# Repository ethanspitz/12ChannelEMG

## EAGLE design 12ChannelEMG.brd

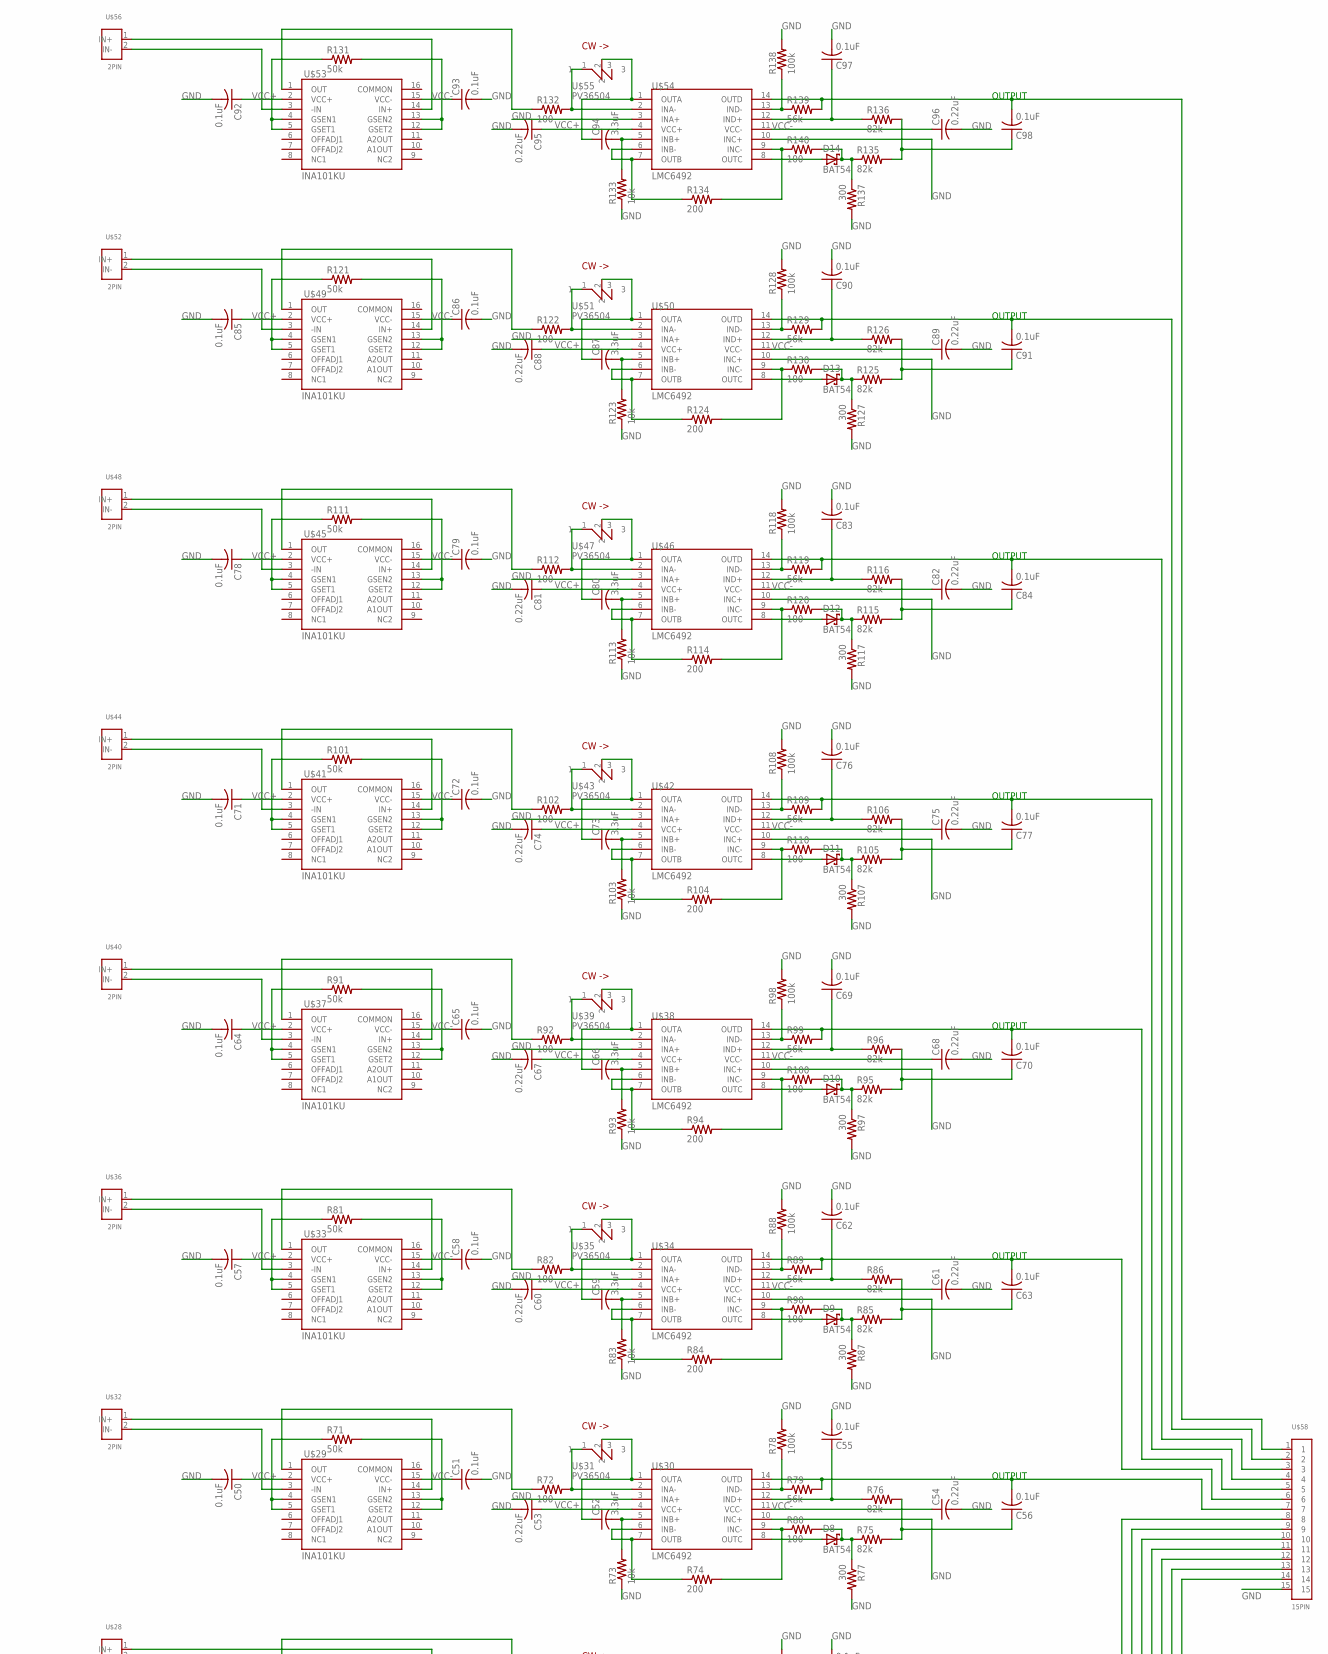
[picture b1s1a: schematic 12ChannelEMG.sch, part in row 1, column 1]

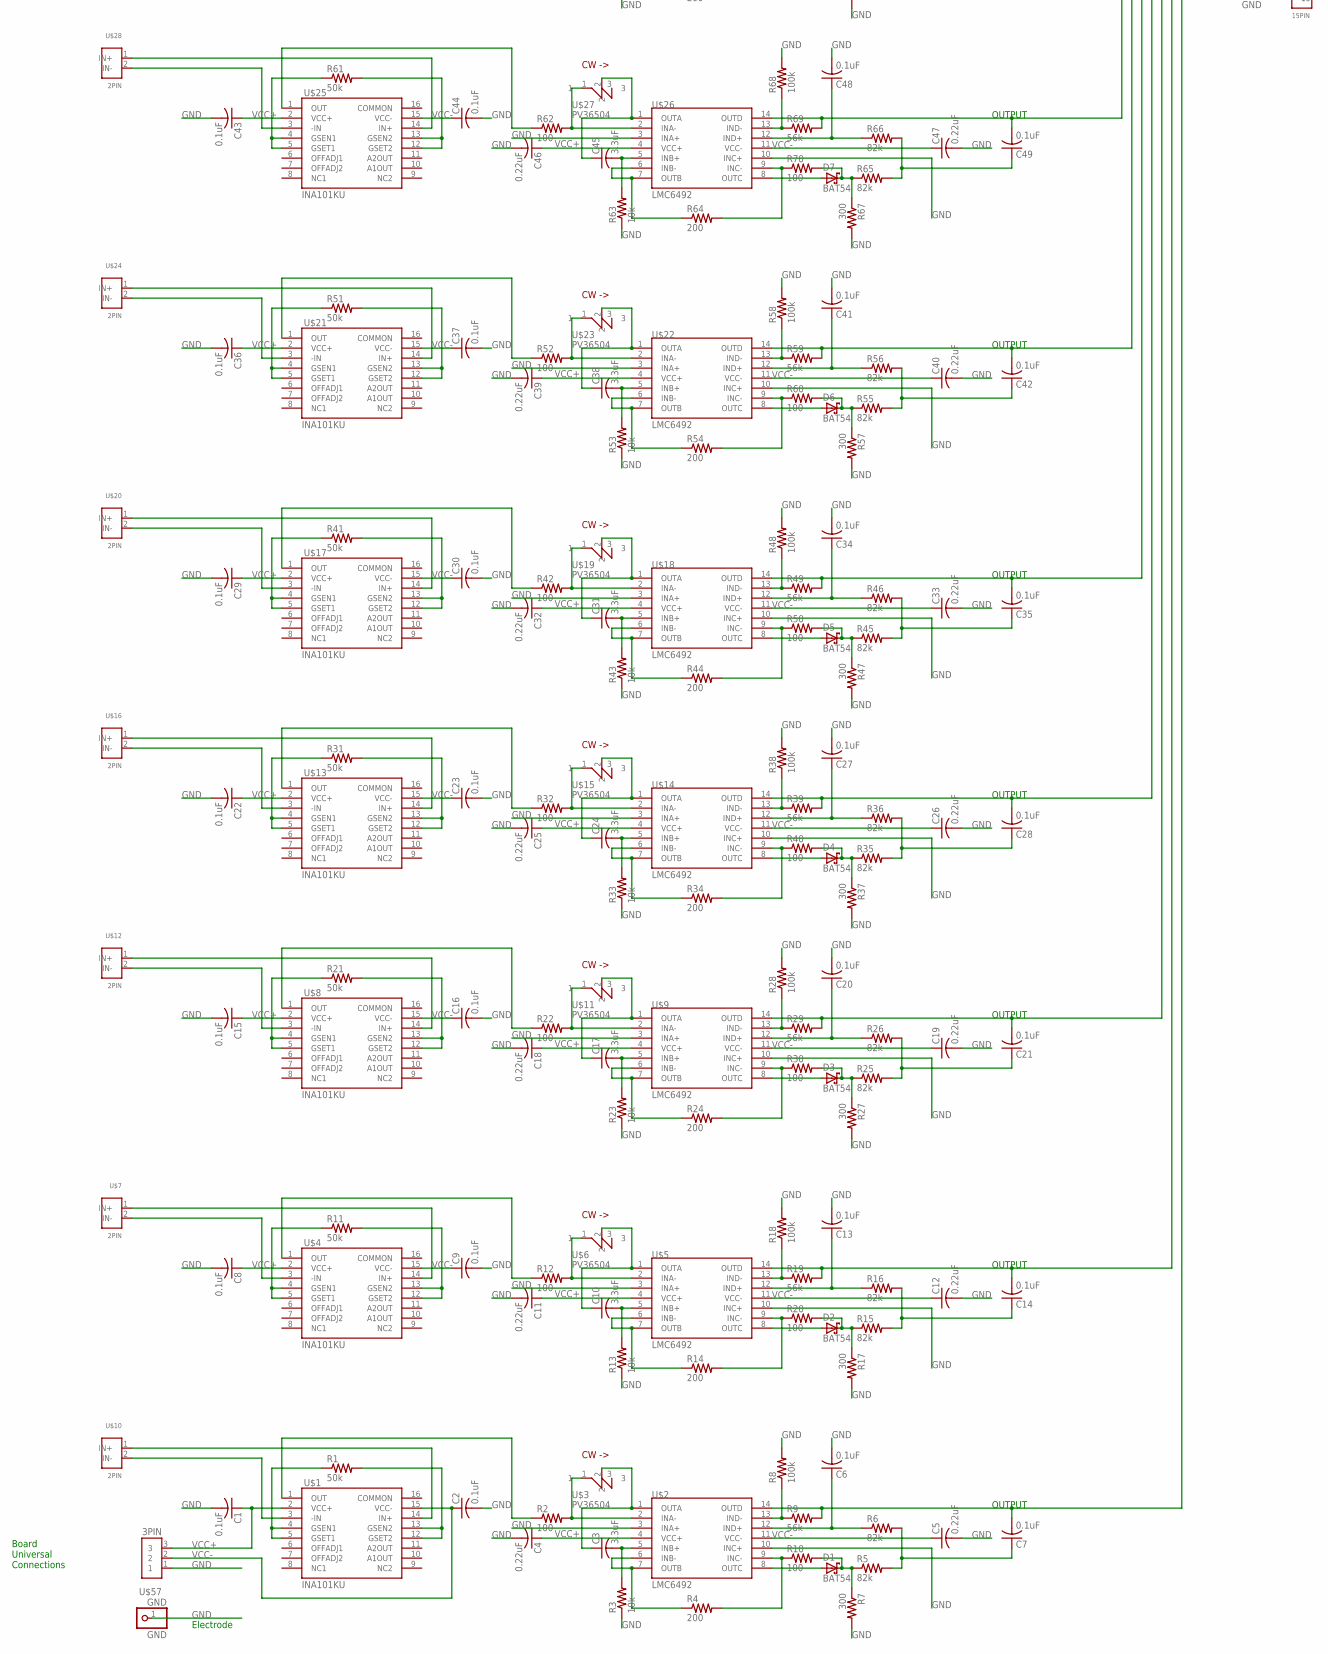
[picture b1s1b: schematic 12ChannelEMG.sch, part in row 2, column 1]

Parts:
C1, C2, C6, C7, C8, C9, C13, C14, C15, C16, C20, C21, C22, C23, C27, C28, C29, C30, C34, C35, C36, C37, C41, C42, C43, C44, C48, C49, C50, C51, C55, C56, C57, C58, C62, C63, C64, C65, C69, C70, C71, C72, C76, C77, C78, C79, C83, C84, C85, C86, C90, C91, C92, C93, C97, C98: 0.1uF; C1206K
C3, C10, C17, C24, C31, C38, C45, C52, C59, C66, C73, C80, C87, C94: 3.3uF; C1206K
C4, C5, C11, C12, C18, C19, C25, C26, C32, C33, C39, C40, C46, C47, C53, C54, C60, C61, C67, C68, C74, C75, C81, C82, C88, C89, C95, C96: 0.22uF; C0603K
D1, D2, D3, D4, D5, D6, D7, D8, D9, D10, D11, D12, D13, D14: BAT54; SOT23
GND: GND; 1X01
R1, R11, R21, R31, R41, R51, R61, R71, R81, R91, R101, R111, R121, R131: 50k; R0805
R2, R10, R12, R20, R22, R30, R32, R40, R42, R50, R52, R60, R62, R70, R72, R80, R82, R90, R92, R100, R102, R110, R112, R120, R122, R130, R132, R140: 100; R0603
R3, R13, R23, R33, R43, R53, R63, R73, R83, R93, R103, R113, R123, R133: 10k; R0603
R4, R14, R24, R34, R44, R54, R64, R74, R84, R94, R104, R114, R124, R134: 200; R0603
R5, R6, R15, R16, R25, R26, R35, R36, R45, R46, R55, R56, R65, R66, R75, R76, R85, R86, R95, R96, R105, R106, R115, R116, R125, R126, R135, R136: 82k; R0603
R7, R17, R27, R37, R47, R57, R67, R77, R87, R97, R107, R117, R127, R137: 300; R0603
R8, R18, R28, R38, R48, R58, R68, R78, R88, R98, R108, R118, R128, R138: 100k; R0603
R9, R19, R29, R39, R49, R59, R69, R79, R89, R99, R109, R119, R129, R139: 56k; R0603
U$1, U$4, U$8, U$13, U$17, U$21, U$25, U$29, U$33, U$37, U$41, U$45, U$49, U$53: INA101KU; SOIC167.5MM
U$2, U$5, U$9, U$14, U$18, U$22, U$26, U$30, U$34, U$38, U$42, U$46, U$50, U$54: LMC6492; SOIC14
U$3, U$6, U$11, U$15, U$19, U$23, U$27, U$31, U$35, U$39, U$43, U$47, U$51, U$55: PV36504; PV36W
U$7, U$10, U$12, U$16, U$20, U$24, U$28, U$32, U$36, U$40, U$44, U$48, U$52, U$56: 2PIN
U$57: 3PIN
U$58: 15PIN

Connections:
GND: C1.2, C2.2, C4.2, C5.2, C6.2, C8.2, C9.2, C11.2, C12.2, C13.2, C15.2, C16.2, C18.2, C19.2, C20.2, C22.2, C23.2, C25.2, C26.2, C27.2, C29.2, C30.2, C32.2, C33.2, C34.2, C36.2, C37.2, C39.2, C40.2, C41.2, C43.2, C44.2, C46.2, C47.2, C48.2, C50.2, C51.2, C53.2, C54.2, C55.2, C57.2, C58.2, C60.2, C61.2, C62.2, C64.2, C65.2, C67.2, C68.2, C69.2, C71.2, C72.2, C74.2, C75.2, C76.2, C78.2, C79.2, C81.2, C82.2, C83.2, C85.2, C86.2, C88.2, C89.2, C90.2, C92.2, C93.2, C95.2, C96.2, C97.2, GND.1, R3.1, R7.2, R8.2, R13.1, R17.2, R18.2, R23.1, R27.2, R28.2, R33.1, R37.2, R38.2, R43.1, R47.2, R48.2, R53.1, R57.2, R58.2, R63.1, R67.2, R68.2, R73.1, R77.2, R78.2, R83.1, R87.2, R88.2, R93.1, R97.2, R98.2, R103.1, R107.2, R108.2, R113.1, R117.2, R118.2, R123.1, R127.2, R128.2, R133.1, R137.2, R138.2, U$2.3 (INA+), U$2.10 (INC+), U$5.3 (INA+), U$5.10 (INC+), U$9.3 (INA+), U$9.10 (INC+), U$14.3 (INA+), U$14.10 (INC+), U$18.3 (INA+), U$18.10 (INC+), U$22.3 (INA+), U$22.10 (INC+), U$26.3 (INA+), U$26.10 (INC+), U$30.3 (INA+), U$30.10 (INC+), U$34.3 (INA+), U$34.10 (INC+), U$38.3 (INA+), U$38.10 (INC+), U$42.3 (INA+), U$42.10 (INC+), U$46.3 (INA+), U$46.10 (INC+), U$50.3 (INA+), U$50.10 (INC+), U$54.3 (INA+), U$54.10 (INC+), U$57.1, U$58.15
unnamed: C3.1, U$2.1 (OUTA), U$3.2
unnamed: R1.2, U$1.12 (GSET2), U$1.13 (GSEN2)
unnamed: C3.2, R3.2, U$2.5 (INB+)
unnamed: R4.1, U$2.6 (INB-), U$2.7 (OUTB)
unnamed: R2.2, U$2.2 (INA-), U$3.1
unnamed: U$1.3 (-IN), U$10.2 (IN-)
unnamed: U$1.14 (IN+), U$10.1 (IN+)
unnamed: R2.1, U$1.1 (OUT)
unnamed: R4.2, R10.1, U$2.9 (INC-)
unnamed: D1.1 (A), U$2.8 (OUTC)
unnamed: C6.1, R6.1, U$2.12 (IND+)
unnamed: D1.3 (C), R5.1, R7.1, R10.2
unnamed: R11.2, U$4.12 (GSET2), U$4.13 (GSEN2)
unnamed: C7.2, R9.2, U$2.14 (OUTD), U$58.14
unnamed: R8.1, R9.1, U$2.13 (IND-)
unnamed: C7.1, R5.2, R6.2
unnamed: R1.1, U$1.4 (GSEN1), U$1.5 (GSET1)
unnamed: U$4.3 (-IN), U$7.2 (IN-)
unnamed: R12.2, U$5.2 (INA-), U$6.1
unnamed: R12.1, U$4.1 (OUT)
unnamed: C10.1, U$5.1 (OUTA), U$6.2
unnamed: C10.2, R13.2, U$5.5 (INB+)
unnamed: R14.1, U$5.6 (INB-), U$5.7 (OUTB)
unnamed: R14.2, R20.1, U$5.9 (INC-)
unnamed: D2.1 (A), U$5.8 (OUTC)
unnamed: C13.1, R16.1, U$5.12 (IND+)
unnamed: D2.3 (C), R15.1, R17.1, R20.2
unnamed: C14.2, R19.2, U$5.14 (OUTD), U$58.13
unnamed: R18.1, R19.1, U$5.13 (IND-)
unnamed: C14.1, R15.2, R16.2
unnamed: R11.1, U$4.4 (GSEN1), U$4.5 (GSET1)
unnamed: U$4.14 (IN+), U$7.1 (IN+)
unnamed: R21.2, U$8.12 (GSET2), U$8.13 (GSEN2)
unnamed: U$8.3 (-IN), U$12.2 (IN-)
unnamed: R22.2, U$9.2 (INA-), U$11.1
unnamed: R22.1, U$8.1 (OUT)
unnamed: C17.1, U$9.1 (OUTA), U$11.2
unnamed: C17.2, R23.2, U$9.5 (INB+)
unnamed: R24.1, U$9.6 (INB-), U$9.7 (OUTB)
unnamed: R24.2, R30.1, U$9.9 (INC-)
unnamed: D3.1 (A), U$9.8 (OUTC)
unnamed: C20.1, R26.1, U$9.12 (IND+)
unnamed: D3.3 (C), R25.1, R27.1, R30.2
unnamed: C21.2, R29.2, U$9.14 (OUTD), U$58.12
unnamed: R28.1, R29.1, U$9.13 (IND-)
unnamed: C21.1, R25.2, R26.2
unnamed: R21.1, U$8.4 (GSEN1), U$8.5 (GSET1)
unnamed: U$8.14 (IN+), U$12.1 (IN+)
unnamed: R31.2, U$13.12 (GSET2), U$13.13 (GSEN2)
unnamed: U$13.3 (-IN), U$16.2 (IN-)
unnamed: R32.2, U$14.2 (INA-), U$15.1
unnamed: R32.1, U$13.1 (OUT)
unnamed: C24.1, U$14.1 (OUTA), U$15.2
unnamed: C24.2, R33.2, U$14.5 (INB+)
unnamed: R34.1, U$14.6 (INB-), U$14.7 (OUTB)
unnamed: R34.2, R40.1, U$14.9 (INC-)
unnamed: D4.1 (A), U$14.8 (OUTC)
unnamed: C27.1, R36.1, U$14.12 (IND+)
unnamed: D4.3 (C), R35.1, R37.1, R40.2
unnamed: C28.2, R39.2, U$14.14 (OUTD), U$58.11
unnamed: R38.1, R39.1, U$14.13 (IND-)
unnamed: C28.1, R35.2, R36.2
unnamed: R31.1, U$13.4 (GSEN1), U$13.5 (GSET1)
unnamed: U$13.14 (IN+), U$16.1 (IN+)
unnamed: R41.2, U$17.12 (GSET2), U$17.13 (GSEN2)
unnamed: U$17.3 (-IN), U$20.2 (IN-)
unnamed: R42.2, U$18.2 (INA-), U$19.1
unnamed: R42.1, U$17.1 (OUT)
unnamed: C31.1, U$18.1 (OUTA), U$19.2
unnamed: C31.2, R43.2, U$18.5 (INB+)
unnamed: R44.1, U$18.6 (INB-), U$18.7 (OUTB)
unnamed: R44.2, R50.1, U$18.9 (INC-)
unnamed: D5.1 (A), U$18.8 (OUTC)
unnamed: C34.1, R46.1, U$18.12 (IND+)
unnamed: D5.3 (C), R45.1, R47.1, R50.2
unnamed: C35.2, R49.2, U$18.14 (OUTD), U$58.10
unnamed: R48.1, R49.1, U$18.13 (IND-)
unnamed: C35.1, R45.2, R46.2
unnamed: R41.1, U$17.4 (GSEN1), U$17.5 (GSET1)
unnamed: U$17.14 (IN+), U$20.1 (IN+)
unnamed: R51.2, U$21.12 (GSET2), U$21.13 (GSEN2)
unnamed: U$21.3 (-IN), U$24.2 (IN-)
unnamed: R52.2, U$22.2 (INA-), U$23.1
unnamed: R52.1, U$21.1 (OUT)
unnamed: C38.1, U$22.1 (OUTA), U$23.2
unnamed: C38.2, R53.2, U$22.5 (INB+)
unnamed: R54.1, U$22.6 (INB-), U$22.7 (OUTB)
unnamed: R54.2, R60.1, U$22.9 (INC-)
unnamed: D6.1 (A), U$22.8 (OUTC)
unnamed: C41.1, R56.1, U$22.12 (IND+)
unnamed: D6.3 (C), R55.1, R57.1, R60.2
unnamed: C42.2, R59.2, U$22.14 (OUTD), U$58.9
unnamed: R58.1, R59.1, U$22.13 (IND-)
unnamed: C42.1, R55.2, R56.2
unnamed: R51.1, U$21.4 (GSEN1), U$21.5 (GSET1)
unnamed: U$21.14 (IN+), U$24.1 (IN+)
unnamed: R61.2, U$25.12 (GSET2), U$25.13 (GSEN2)
unnamed: U$25.3 (-IN), U$28.2 (IN-)
unnamed: R62.2, U$26.2 (INA-), U$27.1
unnamed: R62.1, U$25.1 (OUT)
unnamed: C45.1, U$26.1 (OUTA), U$27.2
unnamed: C45.2, R63.2, U$26.5 (INB+)
unnamed: R64.1, U$26.6 (INB-), U$26.7 (OUTB)
unnamed: R64.2, R70.1, U$26.9 (INC-)
unnamed: D7.1 (A), U$26.8 (OUTC)
unnamed: C48.1, R66.1, U$26.12 (IND+)
unnamed: D7.3 (C), R65.1, R67.1, R70.2
unnamed: C49.2, R69.2, U$26.14 (OUTD), U$58.8
unnamed: R68.1, R69.1, U$26.13 (IND-)
unnamed: C49.1, R65.2, R66.2
unnamed: R61.1, U$25.4 (GSEN1), U$25.5 (GSET1)
unnamed: U$25.14 (IN+), U$28.1 (IN+)
unnamed: R71.2, U$29.12 (GSET2), U$29.13 (GSEN2)
unnamed: U$29.3 (-IN), U$32.2 (IN-)
unnamed: R72.2, U$30.2 (INA-), U$31.1
unnamed: R72.1, U$29.1 (OUT)
unnamed: C52.1, U$30.1 (OUTA), U$31.2
unnamed: C52.2, R73.2, U$30.5 (INB+)
unnamed: R74.1, U$30.6 (INB-), U$30.7 (OUTB)
unnamed: R74.2, R80.1, U$30.9 (INC-)
unnamed: D8.1 (A), U$30.8 (OUTC)
unnamed: C55.1, R76.1, U$30.12 (IND+)
unnamed: D8.3 (C), R75.1, R77.1, R80.2
unnamed: C56.2, R79.2, U$30.14 (OUTD), U$58.7
unnamed: R78.1, R79.1, U$30.13 (IND-)
unnamed: C56.1, R75.2, R76.2
unnamed: R71.1, U$29.4 (GSEN1), U$29.5 (GSET1)
unnamed: U$29.14 (IN+), U$32.1 (IN+)
unnamed: R81.2, U$33.12 (GSET2), U$33.13 (GSEN2)
unnamed: U$33.3 (-IN), U$36.2 (IN-)
unnamed: R82.2, U$34.2 (INA-), U$35.1
unnamed: R82.1, U$33.1 (OUT)
unnamed: C59.1, U$34.1 (OUTA), U$35.2
unnamed: C59.2, R83.2, U$34.5 (INB+)
unnamed: R84.1, U$34.6 (INB-), U$34.7 (OUTB)
unnamed: R84.2, R90.1, U$34.9 (INC-)
unnamed: D9.1 (A), U$34.8 (OUTC)
unnamed: C62.1, R86.1, U$34.12 (IND+)
unnamed: D9.3 (C), R85.1, R87.1, R90.2
unnamed: C63.2, R89.2, U$34.14 (OUTD), U$58.6
unnamed: R88.1, R89.1, U$34.13 (IND-)
unnamed: C63.1, R85.2, R86.2
unnamed: R81.1, U$33.4 (GSEN1), U$33.5 (GSET1)
unnamed: U$33.14 (IN+), U$36.1 (IN+)
unnamed: R91.2, U$37.12 (GSET2), U$37.13 (GSEN2)
unnamed: U$37.3 (-IN), U$40.2 (IN-)
unnamed: R92.2, U$38.2 (INA-), U$39.1
unnamed: R92.1, U$37.1 (OUT)
unnamed: C66.1, U$38.1 (OUTA), U$39.2
unnamed: C66.2, R93.2, U$38.5 (INB+)
unnamed: R94.1, U$38.6 (INB-), U$38.7 (OUTB)
unnamed: R94.2, R100.1, U$38.9 (INC-)
unnamed: D10.1 (A), U$38.8 (OUTC)
unnamed: C69.1, R96.1, U$38.12 (IND+)
unnamed: D10.3 (C), R95.1, R97.1, R100.2
unnamed: C70.2, R99.2, U$38.14 (OUTD), U$58.5
unnamed: R98.1, R99.1, U$38.13 (IND-)
unnamed: C70.1, R95.2, R96.2
unnamed: R91.1, U$37.4 (GSEN1), U$37.5 (GSET1)
unnamed: U$37.14 (IN+), U$40.1 (IN+)
unnamed: R101.2, U$41.12 (GSET2), U$41.13 (GSEN2)
unnamed: U$41.3 (-IN), U$44.2 (IN-)
unnamed: R102.2, U$42.2 (INA-), U$43.1
unnamed: R102.1, U$41.1 (OUT)
unnamed: C73.1, U$42.1 (OUTA), U$43.2
unnamed: C73.2, R103.2, U$42.5 (INB+)
unnamed: R104.1, U$42.6 (INB-), U$42.7 (OUTB)
unnamed: R104.2, R110.1, U$42.9 (INC-)
unnamed: D11.1 (A), U$42.8 (OUTC)
unnamed: C76.1, R106.1, U$42.12 (IND+)
unnamed: D11.3 (C), R105.1, R107.1, R110.2
unnamed: C77.2, R109.2, U$42.14 (OUTD), U$58.4
unnamed: R108.1, R109.1, U$42.13 (IND-)
unnamed: C77.1, R105.2, R106.2
unnamed: R101.1, U$41.4 (GSEN1), U$41.5 (GSET1)
unnamed: U$41.14 (IN+), U$44.1 (IN+)
unnamed: R111.2, U$45.12 (GSET2), U$45.13 (GSEN2)
unnamed: U$45.3 (-IN), U$48.2 (IN-)
unnamed: R112.2, U$46.2 (INA-), U$47.1
unnamed: R112.1, U$45.1 (OUT)
unnamed: C80.1, U$46.1 (OUTA), U$47.2
unnamed: C80.2, R113.2, U$46.5 (INB+)
unnamed: R114.1, U$46.6 (INB-), U$46.7 (OUTB)
unnamed: R114.2, R120.1, U$46.9 (INC-)
unnamed: D12.1 (A), U$46.8 (OUTC)
unnamed: C83.1, R116.1, U$46.12 (IND+)
unnamed: D12.3 (C), R115.1, R117.1, R120.2
unnamed: C84.2, R119.2, U$46.14 (OUTD), U$58.3
unnamed: R118.1, R119.1, U$46.13 (IND-)
unnamed: C84.1, R115.2, R116.2
unnamed: R111.1, U$45.4 (GSEN1), U$45.5 (GSET1)
unnamed: U$45.14 (IN+), U$48.1 (IN+)
unnamed: R121.2, U$49.12 (GSET2), U$49.13 (GSEN2)
unnamed: U$49.3 (-IN), U$52.2 (IN-)
unnamed: R122.2, U$50.2 (INA-), U$51.1
unnamed: R122.1, U$49.1 (OUT)
unnamed: C87.1, U$50.1 (OUTA), U$51.2
unnamed: C87.2, R123.2, U$50.5 (INB+)
unnamed: R124.1, U$50.6 (INB-), U$50.7 (OUTB)
unnamed: R124.2, R130.1, U$50.9 (INC-)
unnamed: D13.1 (A), U$50.8 (OUTC)
unnamed: C90.1, R126.1, U$50.12 (IND+)
unnamed: D13.3 (C), R125.1, R127.1, R130.2
unnamed: C91.2, R129.2, U$50.14 (OUTD), U$58.2
unnamed: R128.1, R129.1, U$50.13 (IND-)
unnamed: C91.1, R125.2, R126.2
unnamed: R121.1, U$49.4 (GSEN1), U$49.5 (GSET1)
unnamed: U$49.14 (IN+), U$52.1 (IN+)
unnamed: R131.2, U$53.12 (GSET2), U$53.13 (GSEN2)
unnamed: U$53.3 (-IN), U$56.2 (IN-)
unnamed: R132.2, U$54.2 (INA-), U$55.1
unnamed: R132.1, U$53.1 (OUT)
unnamed: C94.1, U$54.1 (OUTA), U$55.2
unnamed: C94.2, R133.2, U$54.5 (INB+)
unnamed: R134.1, U$54.6 (INB-), U$54.7 (OUTB)
unnamed: R134.2, R140.1, U$54.9 (INC-)
unnamed: D14.1 (A), U$54.8 (OUTC)
unnamed: C97.1, R136.1, U$54.12 (IND+)
unnamed: D14.3 (C), R135.1, R137.1, R140.2
unnamed: C98.2, R139.2, U$54.14 (OUTD), U$58.1
unnamed: R138.1, R139.1, U$54.13 (IND-)
unnamed: C98.1, R135.2, R136.2
unnamed: R131.1, U$53.4 (GSEN1), U$53.5 (GSET1)
unnamed: U$53.14 (IN+), U$56.1 (IN+)
VCC+: C1.1, C4.1, C8.1, C11.1, C15.1, C18.1, C22.1, C25.1, C29.1, C32.1, C36.1, C39.1, C43.1, C46.1, C50.1, C53.1, C57.1, C60.1, C64.1, C67.1, C71.1, C74.1, C78.1, C81.1, C85.1, C88.1, C92.1, C95.1, U$1.2 (VCC+), U$2.4 (VCC+), U$4.2 (VCC+), U$5.4 (VCC+), U$8.2 (VCC+), U$9.4 (VCC+), U$13.2 (VCC+), U$14.4 (VCC+), U$17.2 (VCC+), U$18.4 (VCC+), U$21.2 (VCC+), U$22.4 (VCC+), U$25.2 (VCC+), U$26.4 (VCC+), U$29.2 (VCC+), U$30.4 (VCC+), U$33.2 (VCC+), U$34.4 (VCC+), U$37.2 (VCC+), U$38.4 (VCC+), U$41.2 (VCC+), U$42.4 (VCC+), U$45.2 (VCC+), U$46.4 (VCC+), U$49.2 (VCC+), U$50.4 (VCC+), U$53.2 (VCC+), U$54.4 (VCC+), U$57.3
VCC-: C2.1, C5.1, C9.1, C12.1, C16.1, C19.1, C23.1, C26.1, C30.1, C33.1, C37.1, C40.1, C44.1, C47.1, C51.1, C54.1, C58.1, C61.1, C65.1, C68.1, C72.1, C75.1, C79.1, C82.1, C86.1, C89.1, C93.1, C96.1, U$1.15 (VCC-), U$2.11 (VCC-), U$4.15 (VCC-), U$5.11 (VCC-), U$8.15 (VCC-), U$9.11 (VCC-), U$13.15 (VCC-), U$14.11 (VCC-), U$17.15 (VCC-), U$18.11 (VCC-), U$21.15 (VCC-), U$22.11 (VCC-), U$25.15 (VCC-), U$26.11 (VCC-), U$29.15 (VCC-), U$30.11 (VCC-), U$33.15 (VCC-), U$34.11 (VCC-), U$37.15 (VCC-), U$38.11 (VCC-), U$41.15 (VCC-), U$42.11 (VCC-), U$45.15 (VCC-), U$46.11 (VCC-), U$49.15 (VCC-), U$50.11 (VCC-), U$53.15 (VCC-), U$54.11 (VCC-), U$57.2

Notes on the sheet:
Electrode
Board Universal Connections
OUTPUT

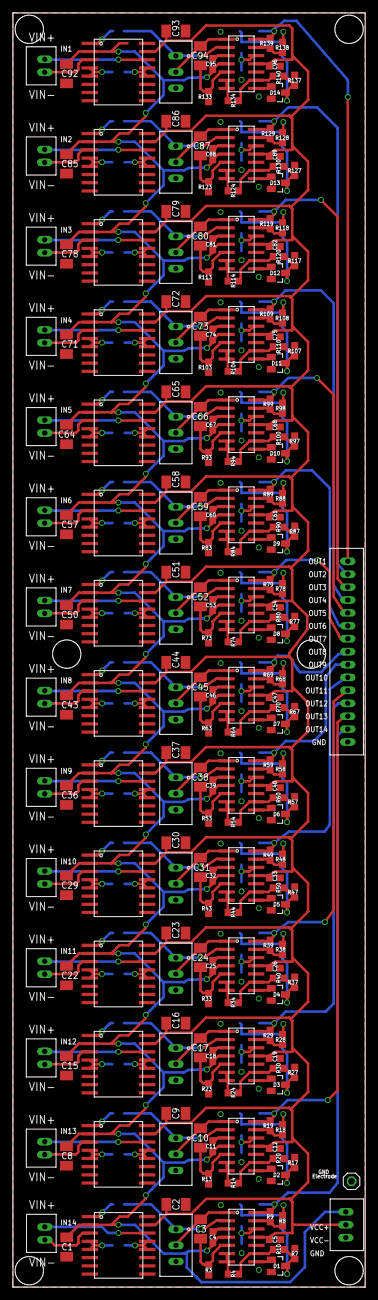
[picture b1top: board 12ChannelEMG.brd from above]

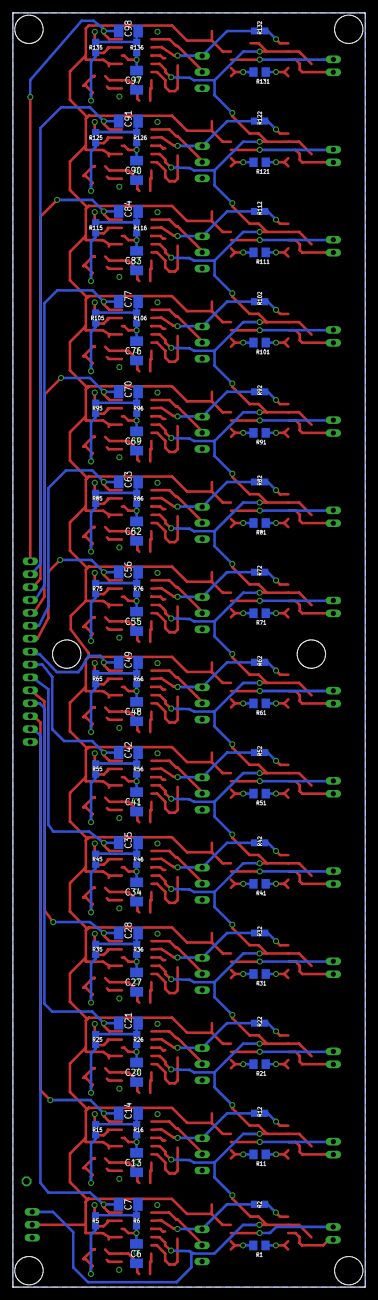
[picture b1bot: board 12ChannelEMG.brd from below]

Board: 2 copper layers, 54.6 x 197.4 mm, 311 parts (84 on the bottom side), 227 nets.

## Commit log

2013-03-21 Initial Commit
    One channel finished.
2013-03-22 Duplicated first channel to make second channel
2013-03-22 Three Channels
2013-03-24 Removed old connectors
    Added ground jumper for ground electrode
2013-03-24 Two channels, problems fixed
2013-03-24 Channel 4
2013-03-24 Channel 6
2013-03-24 Channel 9
2013-03-24 Channel 11
2013-03-24 Channel 14, all channels done
2013-03-24 Added power connector
2013-03-24 Added 15 pin output
    Board finished, need to add silk screen markings
2013-03-24 Shrank board, added silk screening
2013-03-24 Updated Library Parts
2013-03-29 Added Mounting holes in each corner
2013-03-29 Added center mounting holes
